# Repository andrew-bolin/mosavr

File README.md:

# mosavr
Modular Open-Source Audio (Visual?) Receiver

I'm building a modular open-source AV receiver platform, with the following features
- Receive digital audio from TV via HDMI ARC
- Share control signals via HDMI CEC
- Multi-channel audio decoding and amplification
- Multiple outputs
- Apply DSP effects

Use-cases:
- Allow your TV remote to seamlessly control an existing analog amplifier/receiver
- Send a mono mixdown from your home cinema to the bathroom
- Room/speaker compensation
- Start with a 2.0 system, later upgrade to 5.1 

See https://hackaday.io/project/20469-modular-open-source-av-receiver for more detail on progress.

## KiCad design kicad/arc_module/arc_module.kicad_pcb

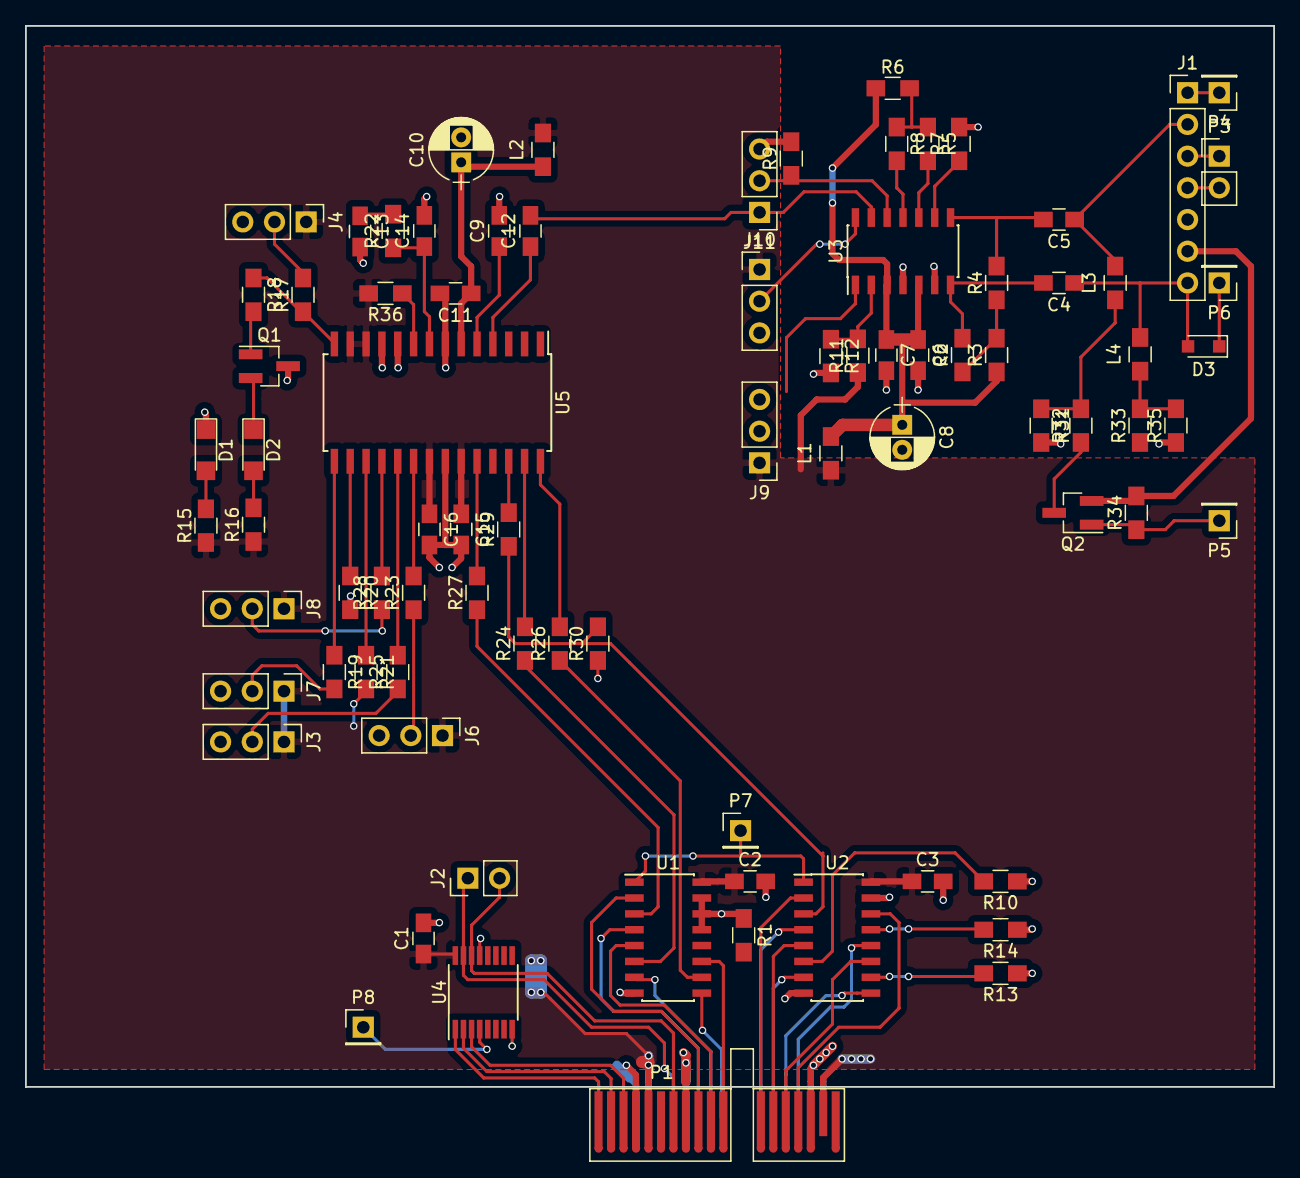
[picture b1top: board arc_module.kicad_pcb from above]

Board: 2 copper layers, 100.0 x 85.0 mm, 83 parts (0 on the bottom side), 80 nets.

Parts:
C1, C2, C3: 0.1uF; C_0805_HandSoldering
C4, C5: 1u; C_0805_HandSoldering
C6, C7, C11, C15, C16: 0.1u; C_0805_HandSoldering
C8: 47u; CP_Radial_D5.0mm_P2.00mm
C9, C12: 0.01u; C_0805_HandSoldering
C10: 10u; CP_Radial_D5.0mm_P2.00mm
C13, C14: C_Small; C_0805_HandSoldering
D1, D2: LED_Small; LED_1206
D3: BAS16H; D_SOD-323_HandSoldering
J1: CONN_01X07; Pin_Header_Straight_1x07_Pitch2.54mm
J2: CONN_01X02; Pin_Header_Straight_1x02_Pitch2.54mm
J3, J4, J6, J7, J8, J9, J10, J11: CONN_01X03; Pin_Header_Straight_1x03_Pitch2.54mm
L1: 300ohm @ 100MHz; L_0805_HandSoldering
L2: Ferrite_Bead_Small; L_0805_HandSoldering
L3, L4: 300; L_0805_HandSoldering
P1: pcie_1x_edge; PCI-EXPRESS
P3: CONN_01X02; Pin_Header_Straight_1x02_Pitch2.54mm
P4, P5, P6, P7, P8: CONN_01X01; Pin_Header_Straight_1x01_Pitch2.54mm
Q1: BC847; SOT-23_Handsoldering
Q2: NTR4502; SOT-23_Handsoldering
R1, R9, R10, R13, R14, R34: 10k; R_0805_HandSoldering
R2, R4, R5, R8: 49.9; R_0805_HandSoldering
R3, R6: 5.1; R_0805_HandSoldering
R7: 39k; R_0805_HandSoldering
R11, R12: 1k; R_0805_HandSoldering
R15, R16, R22: R_Small; R_0805_HandSoldering
R17, R18, R19, R20, R21, R23, R25, R28, R30, R36: 47k; R_0805_HandSoldering
R24, R26, R27, R29: 33R; R_0805_HandSoldering
R31, R35: 5k1; R_0805_HandSoldering
R32, R33: 1k2; R_0805_HandSoldering
U1, U2: 74HCT157; SOIC-16_3.9x9.9mm_Pitch1.27mm
U3: EP91H0; SOIC-14_3.9x8.7mm_Pitch1.27mm
U4: PCA9500; TSSOP-16_4.4x5mm_Pitch0.65mm
U5: CS8416; SOIC-28W_7.5x17.9mm_Pitch1.27mm

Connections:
+3V3: C1.1, C2.1, C3.1, C15.1, C16.1, J3.1, J4.1, J6.1, J7.1, J8.1, J9.1, J10.1, L1.1, L2.2, P1.A5, P1.A17, P1.B5, P1.B17, R11.1, R15.1, R16.1, R21.2, R36.2, U1.16, U2.16, U4.16, U5.12, U5.13, U5.21, U5.23
+5V: J1.6, Q2.2, R34.2
/CEC: J1.1, P4.1
/CS8416/LR_clk: R26.1, U1.10
/CS8416/M_clk: R27.1, U1.3
/CS8416/PDUR: J6.2, R23.1
/CS8416/RM/NV: J4.2, R17.2
/CS8416/RMCF: J8.2, R28.1
/CS8416/SFSEL0: J3.2, R25.1
/CS8416/SFSEL1: J7.2, R19.2
/CS8416/S_clk: R24.1, U1.6
/HDMI_HotPlug: D3.1, P6.1
/HDMI_SCL: J1.3, P3.1
/HDMI_SDA: J1.4, P3.2
/HEAC+: C5.1, J1.2, L3.2
/HEAC-: C4.1, D3.2, J1.7, L4.2
/Module Common/A0: P1.B1, U4.1
/Module Common/A1: P1.B2, U4.2
/Module Common/A2: P1.B3, U4.3
/Module Common/I2S0_in: P1.B12, U2.2
/Module Common/I2S0_mod: R29.1, R30.2, U2.3
/Module Common/I2S0_out: P1.A12, U2.4
/Module Common/I2S1_in: P1.B13, U2.5
/Module Common/I2S1_mod: R10.2, U2.6
/Module Common/I2S1_out: P1.A13, U2.7
/Module Common/I2S2_in: P1.B14, U2.11
/Module Common/I2S2_mod: R13.2, U2.10
/Module Common/I2S2_out: P1.A14, U2.9
/Module Common/I2S3_in: P1.B15, U2.14
/Module Common/I2S3_mod: R14.2, U2.13
/Module Common/I2S3_out: P1.A15, U2.12
/Module Common/IO0: P7.1, P8.1, U1.1, U2.1, U4.4
/Module Common/LRclk_in: P1.B11, U1.11
/Module Common/LRclk_out: P1.A11, U1.9
/Module Common/Mclk_in: P1.B9, U1.2
/Module Common/Mclk_out: P1.A9, U1.4
/Module Common/SCL: J2.2, P1.B7, U4.14
/Module Common/SDA: J2.1, P1.A7, U4.15
/Module Common/Sclk_in: P1.B10, U1.5
/Module Common/Sclk_out: P1.A10, U1.7
/Rx_En: J10.2, U3.14
/SPD_Rx: C12.2, J11.1, U3.13
/SPD_Tx: J11.2, R9.1, U3.12
/Tx_En: J9.2, U3.1
/arc tx/Ctrl_Tx: P5.1, Q2.1, R34.1
GND: C1.2, C2.2, C3.2, C6.2, C7.2, C8.2, C9.2, C10.2, C11.2, C13.2, C14.2, C15.2, C16.2, D1.1, J1.5, J3.3, J4.3, J6.3, J7.3, J8.3, J9.3, J10.3, J11.3, P1.A4, P1.A8, P1.A16, P1.B4, P1.B8, P1.B16, Q1.3, R1.1, R7.2, R9.2, R10.1, R12.2, R13.1, R14.1, R20.2, R30.1, R31.2, R35.1, U1.8, U1.13, U1.14, U1.15, U2.8, U2.15, U3.4, U3.6, U4.8, U4.13, U5.7, U5.10, U5.11, U5.22, U5.25
unnamed: C4.2, R2.2, U3.7
unnamed: C5.2, R4.2, U3.8
unnamed: C9.1, U5.5
unnamed: C10.1, C11.1, L2.1, U5.6
unnamed: C12.1, U5.4
unnamed: C13.1, R22.2
unnamed: C14.1, R22.1, U5.8
unnamed: D1.2, R15.2
unnamed: D2.1, Q1.2
unnamed: D2.2, R16.2
unnamed: L3.1, R31.1, R32.2
unnamed: L4.1, R33.2, R35.2
unnamed: Q1.1, R18.2
unnamed: Q2.3, R32.1, R33.1
unnamed: R1.2, U1.12
unnamed: R2.1, R3.2, R4.1
unnamed: R5.1, R6.2, R8.1
unnamed: R5.2, U3.10
unnamed: R7.1, U3.9
unnamed: R8.2, U3.11
unnamed: R11.2, R12.1, U3.2
unnamed: R17.1, R18.1, U5.14
unnamed: R19.1, U5.15
unnamed: R20.1, U5.16
unnamed: R21.1, U5.17
unnamed: R23.2, U5.20
unnamed: R24.2, U5.27
unnamed: R25.2, U5.19
unnamed: R26.2, U5.28
unnamed: R27.2, U5.24
unnamed: R28.2, U5.18
unnamed: R29.2, U5.26
unnamed: R36.1, U5.9
VDDA: C6.1, C7.1, C8.1, L1.2, R3.1, R6.1, U3.3, U3.5

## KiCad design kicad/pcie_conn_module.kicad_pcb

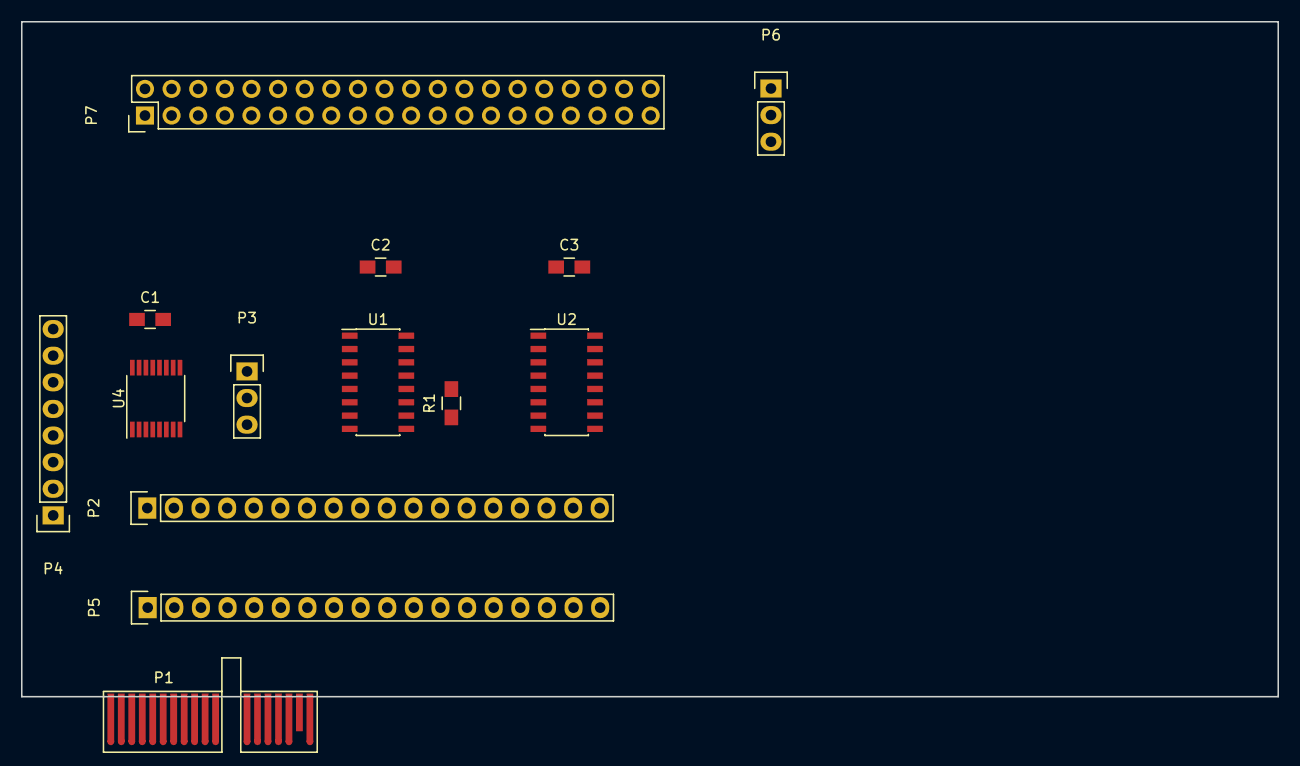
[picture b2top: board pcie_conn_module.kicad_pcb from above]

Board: 2 copper layers, 119.9 x 64.4 mm, 14 parts (0 on the bottom side), 43 nets, no tracks yet.

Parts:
C1, C2, C3: C_Small; C_0805_HandSoldering
P1: pcie_1x_edge; PCI-EXPRESS
P2, P5: CONN_01X18; Pin_Header_Straight_1x18
P3, P6: CONN_01X03; Pin_Header_Straight_1x03
P4: CONN_01X08; Pin_Header_Straight_1x08
P7: CONN_02X20; Pin_Header_Straight_2x20
R1: 10k; R_0805_HandSoldering
U1, U2: 74HCT157; SOIC-16_3.9x9.9mm_Pitch1.27mm
U4: PCA9500; TSSOP-16_4.4x5mm_Pitch0.65mm

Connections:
+3V3: C1.1, C2.1, C3.1, P1.A5, P1.A17, P1.B5, P1.B17, P2.5, P2.17, P3.1, P5.5, P5.17, P7.1, P7.17, U1.16, U2.16, U4.16
+5V: P7.2, P7.4
/A0: P1.B1, P2.1, U4.1
/A1: P1.B2, P2.2, U4.2
/A2: P1.B3, P2.3, U4.3
/I2S0_in: P1.B12, P2.12, U2.2
/I2S0_mod: P6.2, U2.3
/I2S0_out: P1.A12, P5.12, U2.4
/I2S1_in: P1.B13, P2.13, U2.5
/I2S1_out: P1.A13, P5.13, U2.7
/I2S2_in: P1.B14, P2.14, U2.11
/I2S2_out: P1.A14, P5.14, U2.9
/I2S3_in: P1.B15, P2.15, U2.14
/I2S3_out: P1.A15, P5.15, U2.12
/LRclk_in: P1.B11, P2.11, U1.11
/LRclk_out: P1.A11, P5.11, U1.9
/Mclk_in: P1.B9, P2.9, U1.2
/Mclk_out: P1.A9, P5.9, U1.4
/SCL: P1.B7, P2.7, U4.14
/SDA: P1.A7, P5.7, U4.15
/Sclk_in: P1.B10, P2.10, U1.5
/Sclk_out: P1.A10, P5.10, U1.7
/pi_header/I2S_in_to_pi: P6.3, P7.38
/pi_header/I2S_out_from_pi: P6.1, P7.40
GND: C1.2, C2.2, C3.2, P1.A8, P1.A16, P1.B4, P1.B8, P1.B16, P2.4, P2.8, P2.16, P3.3, P5.8, P5.16, P7.6, P7.9, P7.14, P7.20, P7.25, P7.34, P7.39, R1.1, U1.8, U1.13, U1.14, U1.15, U2.8, U2.15, U4.8
unnamed: P1.A1, P5.1
unnamed: P1.A2, P5.2
unnamed: P1.A3, P5.3
unnamed: P1.A4, P5.4
unnamed: P1.A6, P5.6
unnamed: P1.A18, P5.18
unnamed: P1.B6, P2.6
unnamed: P1.B18, P2.18
unnamed: P3.2, U4.13
unnamed: P4.1, U1.1, U2.1, U4.4
unnamed: P4.2, U4.5
unnamed: P4.3, U4.6
unnamed: P4.4, U4.7
unnamed: P4.5, U4.9
unnamed: P4.6, U4.10
unnamed: P4.7, U4.11
unnamed: P4.8, U4.12
unnamed: R1.2, U1.12

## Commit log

2017-03-21 first
2017-03-21 add readme
2017-03-26 mux & eeprom
2017-03-26 add mux & eeprom
2017-03-27 first draft schematic
2017-04-10 v0 PCBs for manufacture
2017-04-11 restructure
2017-04-22 restructure & add ARC
2017-04-23 draft layout
2017-04-23 removed 3v3A
2017-04-23 silkscreen & test points
